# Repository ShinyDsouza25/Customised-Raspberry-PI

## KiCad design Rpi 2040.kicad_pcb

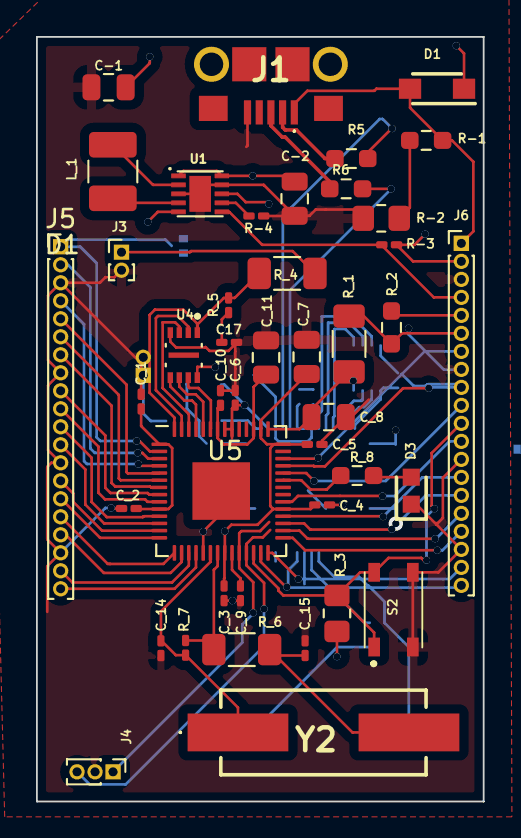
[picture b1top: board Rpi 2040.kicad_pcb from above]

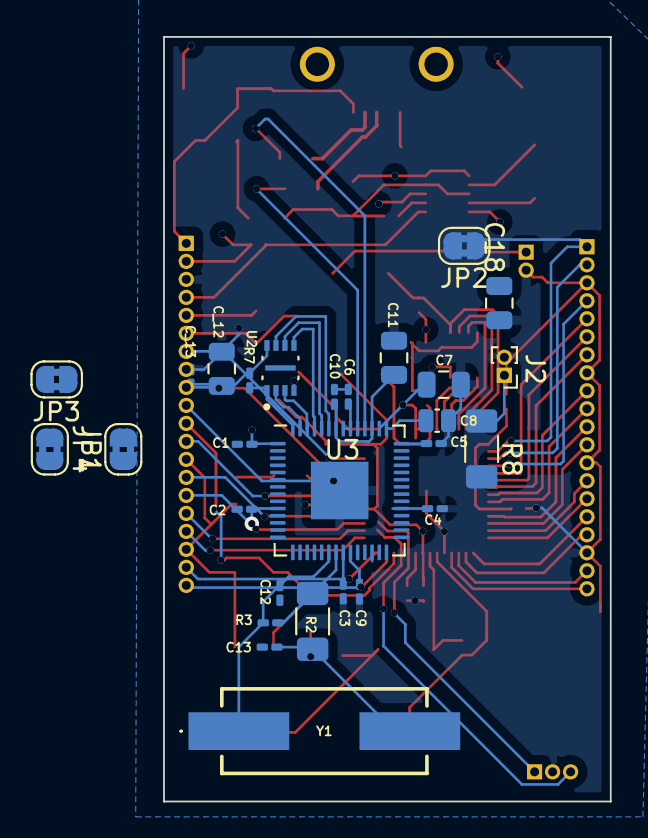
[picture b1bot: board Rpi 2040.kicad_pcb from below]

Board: 4 copper layers, 24.8 x 42.5 mm, 71 parts (28 on the bottom side), 70 nets.

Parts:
C1, C2, C3, C4, C5, C6, C9, C10, C17: 100n; C_0201_0603Metric_Pad0.64x0.40mm_HandSolder
C7, C11, C18: 2u2; C_0805_2012Metric
C8: 1u; C_0504_1310Metric_Pad0.83x1.28mm_HandSolder
C12, C13: 18p; C_0201_0603Metric_Pad0.64x0.40mm_HandSolder
C-1, C-2: 47u; C_0805_2012Metric
C_1, C_2, C_3, C_4, C_5, C_6, C_9, C_10, C_13: 100n; C_0201_0603Metric_Pad0.64x0.40mm_HandSolder
C_7, C_8, C_11, C_12: 2u2; C_0805_2012Metric
C_14, C_15: 18p; C_0201_0603Metric_Pad0.64x0.40mm_HandSolder
D1: D_Schottky; SODFL3616X98N
D3: LED; LEDC1608X80N
J1: USB_B_Micro; 101181930001LF
J2, J3: Conn_01x02; PinHeader_1x02_P1.00mm_Vertical
J4: Conn_01x03; PinHeader_1x03_P1.00mm_Vertical
J5, J6: Conn_01x20; PinHeader_1x20_P1.00mm_Vertical
JP1, JP2, JP3, JP4: SolderJumper_2_Bridged; SolderJumper-2_P1.3mm_Bridged2Bar_RoundedPad1.0x1.5mm
L_1: 2u2; L_1210_3225Metric_Pad1.42x2.65mm_HandSolder
R2: 1k; R_1206_3216Metric_Pad1.30x1.75mm_HandSolder
R3, R7: DNP; R_0201_0603Metric_Pad0.64x0.40mm_HandSolder
R5, R6: 27; R_0603_1608Metric_Pad0.98x0.95mm_HandSolder
R8: 1K; R_1206_3216Metric_Pad1.30x1.75mm_HandSolder
R-1: 5K6; R_0603_1608Metric_Pad0.98x0.95mm_HandSolder
R-2: 10K; R_0805_2012Metric_Pad1.20x1.40mm_HandSolder
R-3, R-4: 100k; R_0201_0603Metric_Pad0.64x0.40mm_HandSolder
R_1: 1R; R_1206_3216Metric_Pad1.30x1.75mm_HandSolder
R_2: 200R; R_0603_1608Metric_Pad0.98x0.95mm_HandSolder
R_3: 10k; R_0805_2012Metric_Pad1.20x1.40mm_HandSolder
R_4: 1K; R_1206_3216Metric_Pad1.30x1.75mm_HandSolder
R_5, R_7: DNP; R_0201_0603Metric_Pad0.64x0.40mm_HandSolder
R_6: 1k; R_1206_3216Metric_Pad1.30x1.75mm_HandSolder
R_8: 470; R_0603_1608Metric_Pad0.98x0.95mm_HandSolder
S2: PTS810SJK250SMTRLFS; PTS810SJG250SMTRLFS
U1: RT6150B-33GQW; SON50P250X250X80-11N
U2, U4: W25Q16JVUXIQ_TR; IC_W25Q16JVUXIQ_TR
U3: RP2040 debugger; QFN-56-1EP_7x7mm_P0.4mm_EP3.2x3.2mm
U5: RP2040 target; QFN-56-1EP_7x7mm_P0.4mm_EP3.2x3.2mm
Y1, Y2: 12MHz; ABLS

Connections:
3V3_EN: J6.4, R-3.2, U1.6 (EN)
/TARGET/1V1: C_9.1, C_10.1, C_11.1, U5.23 (DVDD), U5.45 (VREG_VOUT), U5.50 (DVDD)
/TARGET/3V3: C1.1, C2.1, C3.1, C4.1, C5.1, C6.1, C7.1, C8.2, C17.1, C18.1, C-2.1, C_1.1, C_2.1, C_3.1, C_4.1, C_5.1, C_6.1, C_7.1, C_12.1, C_13.1, J6.5, R7.1, R_2.1, R_3.2, R_5.1, U1.1 (VOUT), U1.10 (FB), U2.8 (VCC), U3.1 (IOVDD), U3.10 (IOVDD), U3.22 (IOVDD), U3.33 (IOVDD), U3.42 (IOVDD), U3.43 (ADC_AVDD), U3.44 (VREG_IN), U3.48 (USB_VDD), U3.49 (IOVDD), U4.8 (VCC), U5.1 (IOVDD), U5.10 (IOVDD), U5.22 (IOVDD), U5.33 (IOVDD), U5.42 (IOVDD), U5.44 (VREG_IN), U5.48 (USB_VDD), U5.49 (IOVDD)
/TARGET/GPIO0: J5.1, JP2.1 (A), JP3.2 (B), U5.2 (GPIO0)
/TARGET/GPIO1: J5.2, JP1.1 (A), JP4.2 (B), U5.3 (GPIO1)
/TARGET/GPIO2: J5.4, U5.4 (GPIO2)
/TARGET/GPIO3: J5.5, U5.5 (GPIO3)
/TARGET/GPIO4: J5.6, U5.6 (GPIO4)
/TARGET/GPIO5: J5.7, U5.7 (GPIO5)
/TARGET/GPIO6: J5.9, U5.8 (GPIO6)
/TARGET/GPIO7: J5.10, U5.9 (GPIO7)
/TARGET/GPIO8: J5.11, U5.11 (GPIO8)
/TARGET/GPIO9: J5.12, U5.12 (GPIO9)
/TARGET/GPIO10: J5.14, U5.13 (GPIO10)
/TARGET/GPIO11: J5.15, U5.14 (GPIO11)
/TARGET/GPIO12: J5.16, U5.15 (GPIO12)
/TARGET/GPIO13: J5.17, U5.16 (GPIO13)
/TARGET/GPIO14: J5.19, U5.17 (GPIO14)
/TARGET/GPIO15: J5.20, U5.18 (GPIO15)
/TARGET/GPIO16: J6.20, U5.27 (GPIO16)
/TARGET/GPIO17: J6.19, U5.28 (GPIO17)
/TARGET/GPIO18: J6.17, U5.29 (GPIO18)
/TARGET/GPIO19: J6.16, U5.30 (GPIO19)
/TARGET/GPIO20: J6.15, U5.31 (GPIO20)
/TARGET/GPIO21: J6.14, U5.32 (GPIO21)
/TARGET/GPIO22: J6.12, U5.34 (GPIO22)
/TARGET/GPIO25: R_8.1, U5.37 (GPIO25)
/TARGET/GPIO26_ADC0: J6.10, U5.38 (GPIO26_ADC0)
/TARGET/GPIO27_ADC1: J6.9, U5.39 (GPIO27_ADC1)
/TARGET/GPIO28_ADC2: J6.7, U5.40 (GPIO28_ADC2)
/TARGET/QSPI_CS: R_4.2, R_5.2, U4.1 (~CS), U5.56 (QSPI_SS)
/TARGET/QSPI_SCK: U4.6 (CLK), U5.52 (QSPI_SCLK)
/TARGET/QSPI_SD0: U4.5 (DI/IO0), U5.53 (QSPI_SD0)
/TARGET/QSPI_SD1: U4.2 (DO/IO1), U5.55 (QSPI_SD1)
/TARGET/QSPI_SD2: U4.3 (~WP~{/IO2), U5.54 (QSPI_SD2)
/TARGET/QSPI_SD3: U4.7 (~HOLD~{/~{RESET~{/IO3), U5.51 (QSPI_SD3)
/TARGET/RUN: J6.11, R_3.1, S2.1, S2.2, U5.26 (RUN)
/TARGET/XIN: C_14.1, R_7.1, U5.20 (XIN), Y2.1
/TARGET/XOUT: R_6.2, R_7.2, U5.21 (XOUT)
/debugger/1V1: C9.1, C10.1, C11.1, U3.23 (DVDD), U3.45 (VREG_VOUT), U3.50 (DVDD)
/debugger/QSPI_CS: R7.2, R8.2, U2.1 (~CS), U3.56 (QSPI_SS)
/debugger/QSPI_SCK: U2.6 (CLK), U3.52 (QSPI_SCLK)
/debugger/QSPI_SD0: U2.5 (DI/IO0), U3.53 (QSPI_SD0)
/debugger/QSPI_SD1: U2.2 (DO/IO1), U3.55 (QSPI_SD1)
/debugger/QSPI_SD2: U2.3 (~WP~{/IO2), U3.54 (QSPI_SD2)
/debugger/QSPI_SD3: U2.7 (~HOLD~{/~{RESET~{/IO3), U3.51 (QSPI_SD3)
/debugger/USB_DM: R5.2, U3.46 (USB_DM)
/debugger/USB_DP: R6.2, U3.47 (USB_DP)
/debugger/XIN: C12.1, R3.1, U3.20 (XIN), Y1.1
/debugger/XOUT: R2.2, R3.2, U3.21 (XOUT)
ADC_VREF: J6.6, R_1.1, R_2.2
GND: C1.2, C2.2, C3.2, C4.2, C5.2, C6.2, C7.2, C8.1, C9.2, C10.2, C11.2, C12.2, C13.2, C17.2, C18.2, C-1.2, C-2.2, C_1.2, C_2.2, C_3.2, C_4.2, C_5.2, C_6.2, C_7.2, C_8.2, C_9.2, C_10.2, C_11.2, C_12.2, C_13.2, C_14.2, C_15.2, D3.1 (K), J1.5 (GND), J2.2, J3.2, J4.2, J5.3, J5.8, J5.13, J5.18, J6.3, J6.8, J6.13, J6.18, R-2.2, R-4.2, S2.3, S2.4, U1.3 (GND), U1.9 (GND), U1.11 (EXP), U2.4 (GND), U3.19 (TESTEN), U3.57 (GND), U4.4 (GND), U5.19 (TESTEN), U5.57 (GND)
GPIO23: R-4.1, U1.7 (PS), U3.35 (GPIO23), U5.35 (GPIO23)
GPIO24: R-1.2, R-2.1, U3.36 (GPIO24), U5.36 (GPIO24)
unnamed: C13.1, R2.1, Y1.2
unnamed: C_8.1, R_1.2, U5.43 (ADC_AVDD)
unnamed: C_15.1, R_6.1, Y2.2
unnamed: D3.2 (A), R_8.2
unnamed: J2.1, R8.1
unnamed: J3.1, R_4.1
unnamed: L_1.1, U1.2 (LX2)
unnamed: L_1.2, U1.4 (LX1)
SWCLK: J4.1, U3.4 (GPIO2), U5.24 (SWCLK)
SWDIO: J4.3, U3.5 (GPIO3), U5.25 (SWD)
TARGET_RX: JP1.2 (B), JP4.1 (A), U3.6 (GPIO4)
TARGET_TX: JP2.2 (B), JP3.1 (A), U3.7 (GPIO5)
USB_P+: J1.3 (D+), R6.1
USB_P-: J1.2 (D-), R5.1
VBUS: D1.2 (A), J1.1 (VBUS), J6.1, R-1.1
VSYS: C-1.1, D1.1 (K), J6.2, R-3.1, U1.5 (VIN), U1.8 (VINA)
